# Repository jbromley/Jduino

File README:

Jduino
======

These are the design files (EAGLE 6) for a simple, homebrew Arduino
clone. It uses the Arduino clone from chapter 6 of _Arduino Robotics_
and seeks to make a smaller board that preserves the Arduino
outline. Additionally, I hope to add the following features:

 * power switch,
 * power protection diode,
 * smaller L4931 LDO voltage regulator,
 * right angle FTDI port on edge of board so programming can be done
   with a shield attached.

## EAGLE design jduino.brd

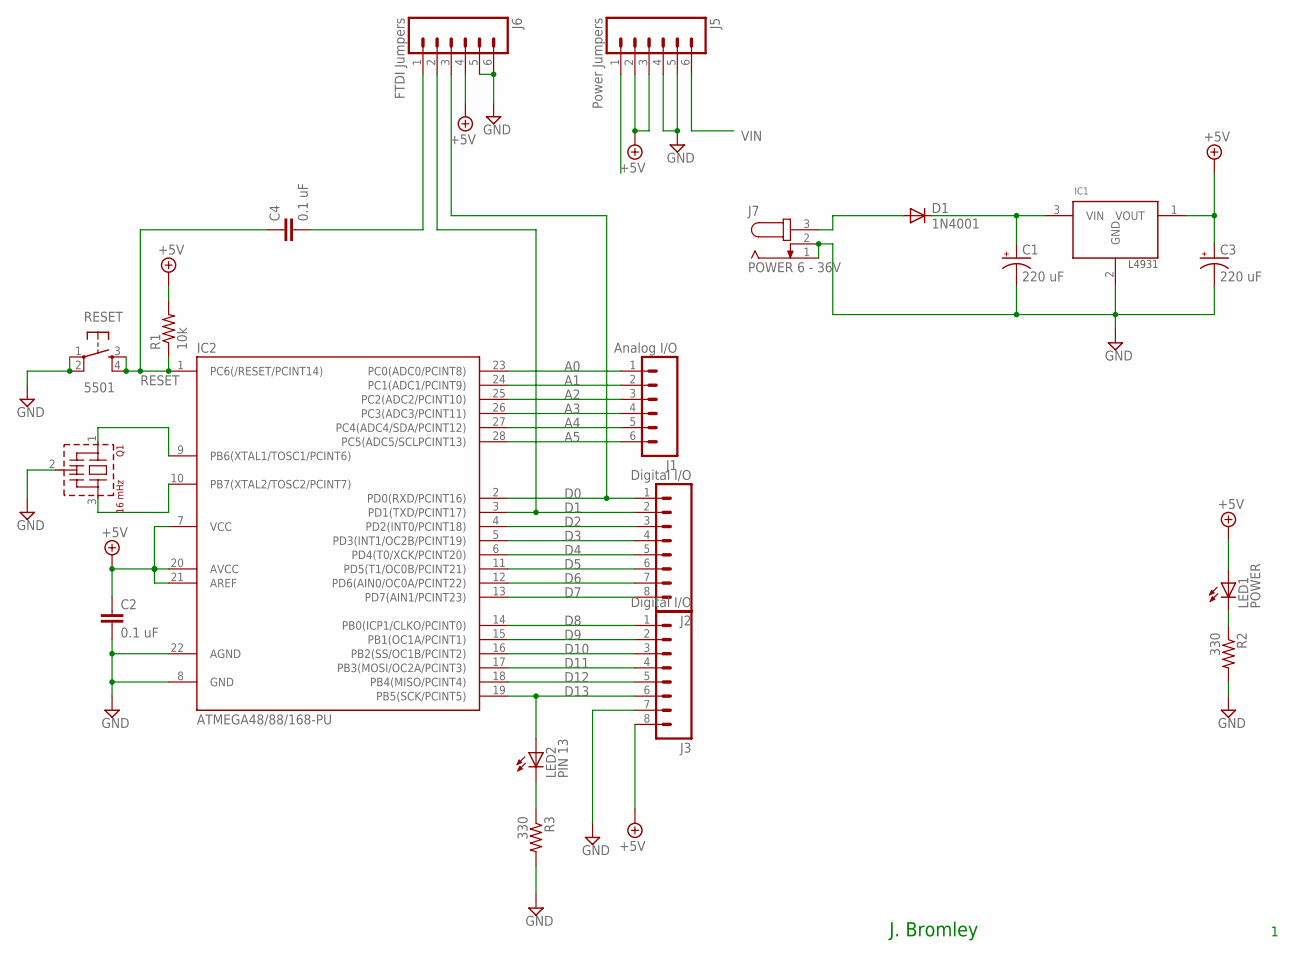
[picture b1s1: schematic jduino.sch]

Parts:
C1, C3: 220 uF; CPOL-RADIAL-10UF-25V
C2, C4: 0.1 uF; CAP-PTH-SMALL
D1: 1N4001; DIODE-1N4001
IC1: L4931; TO-92
IC2: ATMEGA48/88/168-PU; DIL28-3
J1: Analog I/O; 1X06
J2, J3: Digital I/O; 1X08
J5: Power Jumpers; 1X06
J6: FTDI Jumpers; 1X06
J7: POWER 6 - 36V; SPC4078
LED1: POWER; LED3MM
LED2: PIN 13; LED3MM
Q1: 16 mHz; CSTLS_X
R1: 10k; AXIAL-0.3
R2, R3: 330; AXIAL-0.3
RESET: 5501; TACTILE-PTH

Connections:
+5V: C2.1, C3.1 (+), IC1.1 (VOUT), IC2.7 (VCC), IC2.20 (AVCC), IC2.21 (AREF), J3.8, J5.2, J5.3, J6.4, LED1.A, R1.P$2 (2)
A0: IC2.23 (PC0(ADC0/PCINT8)), J1.1
A1: IC2.24 (PC1(ADC1/PCINT9)), J1.2
A2: IC2.25 (PC2(ADC2/PCINT10)), J1.3
A3: IC2.26 (PC3(ADC3/PCINT11)), J1.4
A4: IC2.27 (PC4(ADC4/SDA/PCINT12)), J1.5
A5: IC2.28 (PC5(ADC5/SCLPCINT13)), J1.6
D0: IC2.2 (PD0(RXD/PCINT16)), J2.1, J6.3
D1: IC2.3 (PD1(TXD/PCINT17)), J2.2, J6.2
D2: IC2.4 (PD2(INT0/PCINT18)), J2.3
D3: IC2.5 (PD3(INT1/OC2B/PCINT19)), J2.4
D4: IC2.6 (PD4(T0/XCK/PCINT20)), J2.5
D5: IC2.11 (PD5(T1/OC0B/PCINT21)), J2.6
D6: IC2.12 (PD6(AIN0/OC0A/PCINT22)), J2.7
D7: IC2.13 (PD7(AIN1/PCINT23)), J2.8
D8: IC2.14 (PB0(ICP1/CLKO/PCINT0)), J3.1
D9: IC2.15 (PB1(OC1A/PCINT1)), J3.2
D10: IC2.16 (PB2(SS/OC1B/PCINT2)), J3.3
D11: IC2.17 (PB3(MOSI/OC2A/PCINT3)), J3.4
D12: IC2.18 (PB4(MISO/PCINT4)), J3.5
D13: IC2.19 (PB5(SCK/PCINT5)), J3.6, LED2.A
GND: C1.2 (-), C2.2, C3.2 (-), IC1.2 (GND), IC2.8 (GND), IC2.22 (AGND), J3.7, J5.4, J5.5, J6.5, J6.6, J7.1, J7.2, Q1.2 (VSS), R2.P$2 (2), R3.P$2 (2), RESET.1, RESET.2
unnamed: C4.2, J6.1
unnamed: D1.A, J7.3
unnamed: IC2.10 (PB7(XTAL2/TOSC2/PCINT7)), Q1.3
unnamed: LED2.K (C), R3.P$1 (1)
unnamed: IC2.9 (PB6(XTAL1/TOSC1/PCINT6)), Q1.1
unnamed: C1.1 (+), D1.C, IC1.3 (VIN)
unnamed: LED1.K (C), R2.P$1 (1)
RESET: C4.1, IC2.1 (PC6(/RESET/PCINT14)), J5.1, R1.P$1 (1), RESET.3, RESET.4
VIN: J5.6

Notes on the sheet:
J. Bromley

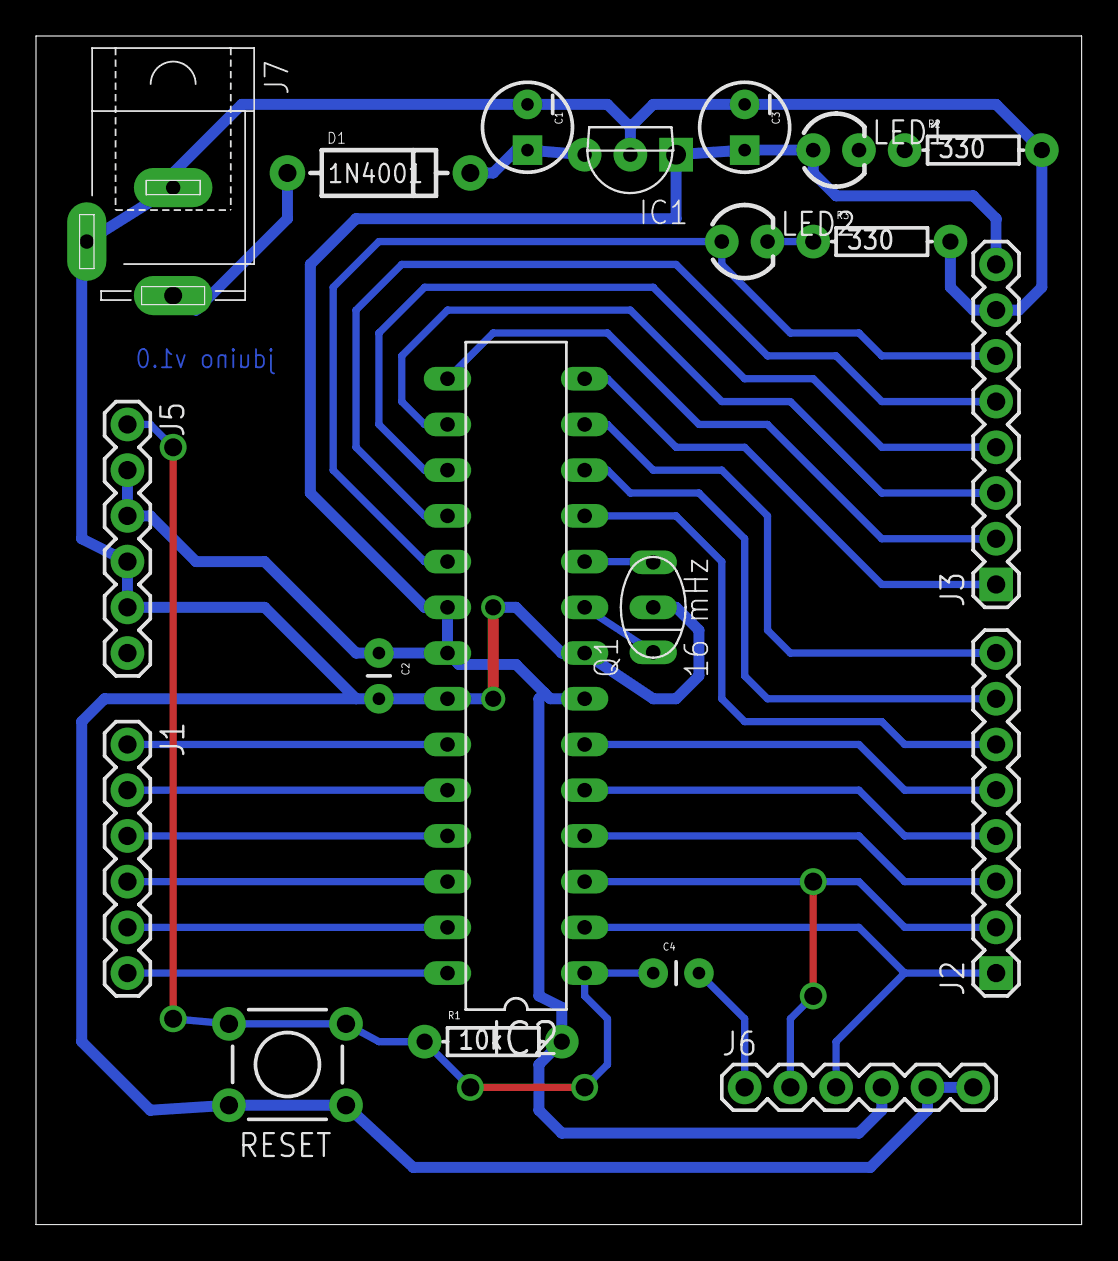
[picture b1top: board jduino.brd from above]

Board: 2 copper layers, 58.1 x 66.0 mm, 20 parts (0 on the bottom side), 30 nets.

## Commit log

2012-03-27 Initial import.
    Initial import of the design files from the _Arduino Robotics_ book.
2012-03-30 Added power elements.
    Added a protection diode and a power switch. Also swapped out the
    7805 for a LDO regulator.
2012-03-30 Initial complete version.
    Routed D9 - D13, GND, and AREF to the headers. Rotated the FTDI
    header to be able to use a right angle header. Two jumpers remain.
2012-04-11 Replaced Euro-stype capacitors.
    Replaced the large reset capacitors with smaller-package 0.1 uF
    capacitors.
2012-04-11 Hand routed some pins.
    I hand-routed pins 3 through 5 and 23 through 28, since these should
    be straight-shots. Then auto routed the remaining traces. The board
    still needs significant cleanup.
2012-04-12 Finished one-sided layout.
    Completed a one-sided layout of the board that only requires three
    jumpers.
2012-04-12 Recentered circuit on board.
    That last revisions left some traces too near the edge of the
    board. Moved the circuit to have at least 0.1 inch clearance on all
    board edges.
2012-04-12 Reset adjustments and aesthetic improvements.
    Connected reset pin on power jumper before DTR capacitor. Cleaned
    up extraneous label and added a frame to the schematic.
2012-05-08 Added mounting holes to the board.
2013-07-03 Completed layout.
    Completed the board layout and sizing. Needed to include four top-side
    jumpers.
2013-07-03 Added a ground plane.
    Made the ground plane encompass the whole board.
2013-07-03 Initial attempt at hand routing.
    The ATmega needs to be moved to the left to allow enough space to
    route all of the digital I/O pins.
2013-07-05 Final fixes for printing.
    Replaced power IC with 2931. Added an LED on pin 13.
2013-07-08 Small fixes to the circuit.
2013-07-13 Cleaned up area around reset button.
    Rotated the reset button. Tied extra button terminals to the live
    terminals.
2013-07-20 Fixed pad sizes.
    Replaced original parts from the Arduino robotics book with components
    from the SparkFun libraries so that pads would be properly sized.

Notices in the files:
parts and their libraries:
SparkFun-Passives: Licensing: CC v3.0 Share-Alike You are welcome to use this library for commercial purposes.
SparkFun-Aesthetics: Released under the Creative Commons
SparkFun-Aesthetics: http://creativecommons.org/licenses/by-sa/3.0
